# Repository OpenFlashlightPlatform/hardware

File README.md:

# Blue Sun OFP

The Blue Sun Open Flashlight Platform is an open source (both hardware and software)
attempt at creating a software-defined ultra-reliable high-performance flashlight.

This project was inspired by the AvE Midnight Sun project, and is intended to match
with the mechanicals developed there, both physically and in spirit. To that end,
a core set of specifications were identified:

 0. The project must be fun. This rule can be applied to override any subsequent
    rule.
 1. The design must be skookum. If in doubt as to the actual definition of "skookum"
    just go balls to the wall and hope the result is sufficiently epic.
 2. The platform should be capable of driving a diverse range of COBs at up to
    160W (40V / 4A). Ensure that in every aspect of the circuit, rule 1 is
    strongly enforced, so that excursions beyond 160W are tolerated and the
    circuit can dynamically detect and react to overload.
 3. The driver should have fine-grained current-mode control of the COB.
 4. The platform should operate from a 3s LiPo battery, and be capable of charging it
    from a 12V source. Naturally, transients, noise and polarity inversions on this
    source must be tolerated. Furthermore, all best practices for LiPo operation
    must be followed including UVLO, cell balancing and temperature monitoring.
 5. The platform should be accessible and open source at every possible level.
    To that end, it should be compatible out-of-the box with an Arduino IDE
    and programmable without any non-free tools, software or licenses.
 6. The circuit must be implemented in the spirit of Rule 1. Everything must be
    resistant to temperature, humidity, vibration, ESD, overvoltage, cell imbalance,
    and short circuit. The circuit must continue to function after being shaken
    in a container of salty boiling water mixed with conductive metal powder.
 7. Every net in the circuit, including internal nets and power supply rails,
    must pass IEC 61000-4-2 (25kV) and IEC 61004-4 (40A) ESD resistance tests.
 8. The firmware itself, both in source form and compiled form, must adhere to
    rule 1. In particular, wherever possible (in that it does not contradict rule
    5), the firmware should be MISRA C:2012 compliant.
 9. Every aspect of the project must be well documented. If the primary maintainer
    were to become unavailable, the community ought to be able to pick up and
    continue.

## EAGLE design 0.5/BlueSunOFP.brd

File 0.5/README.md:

# Version 0.5

This is a prototype iteration, that has no battery charging features. It is so that I can work on the hardware and firmware in parallel.

It should in theory work for up to 160W COBs. I'll be testing that at a later stage.

The BOM is also available as a google doc here: https://goo.gl/zxzSkw

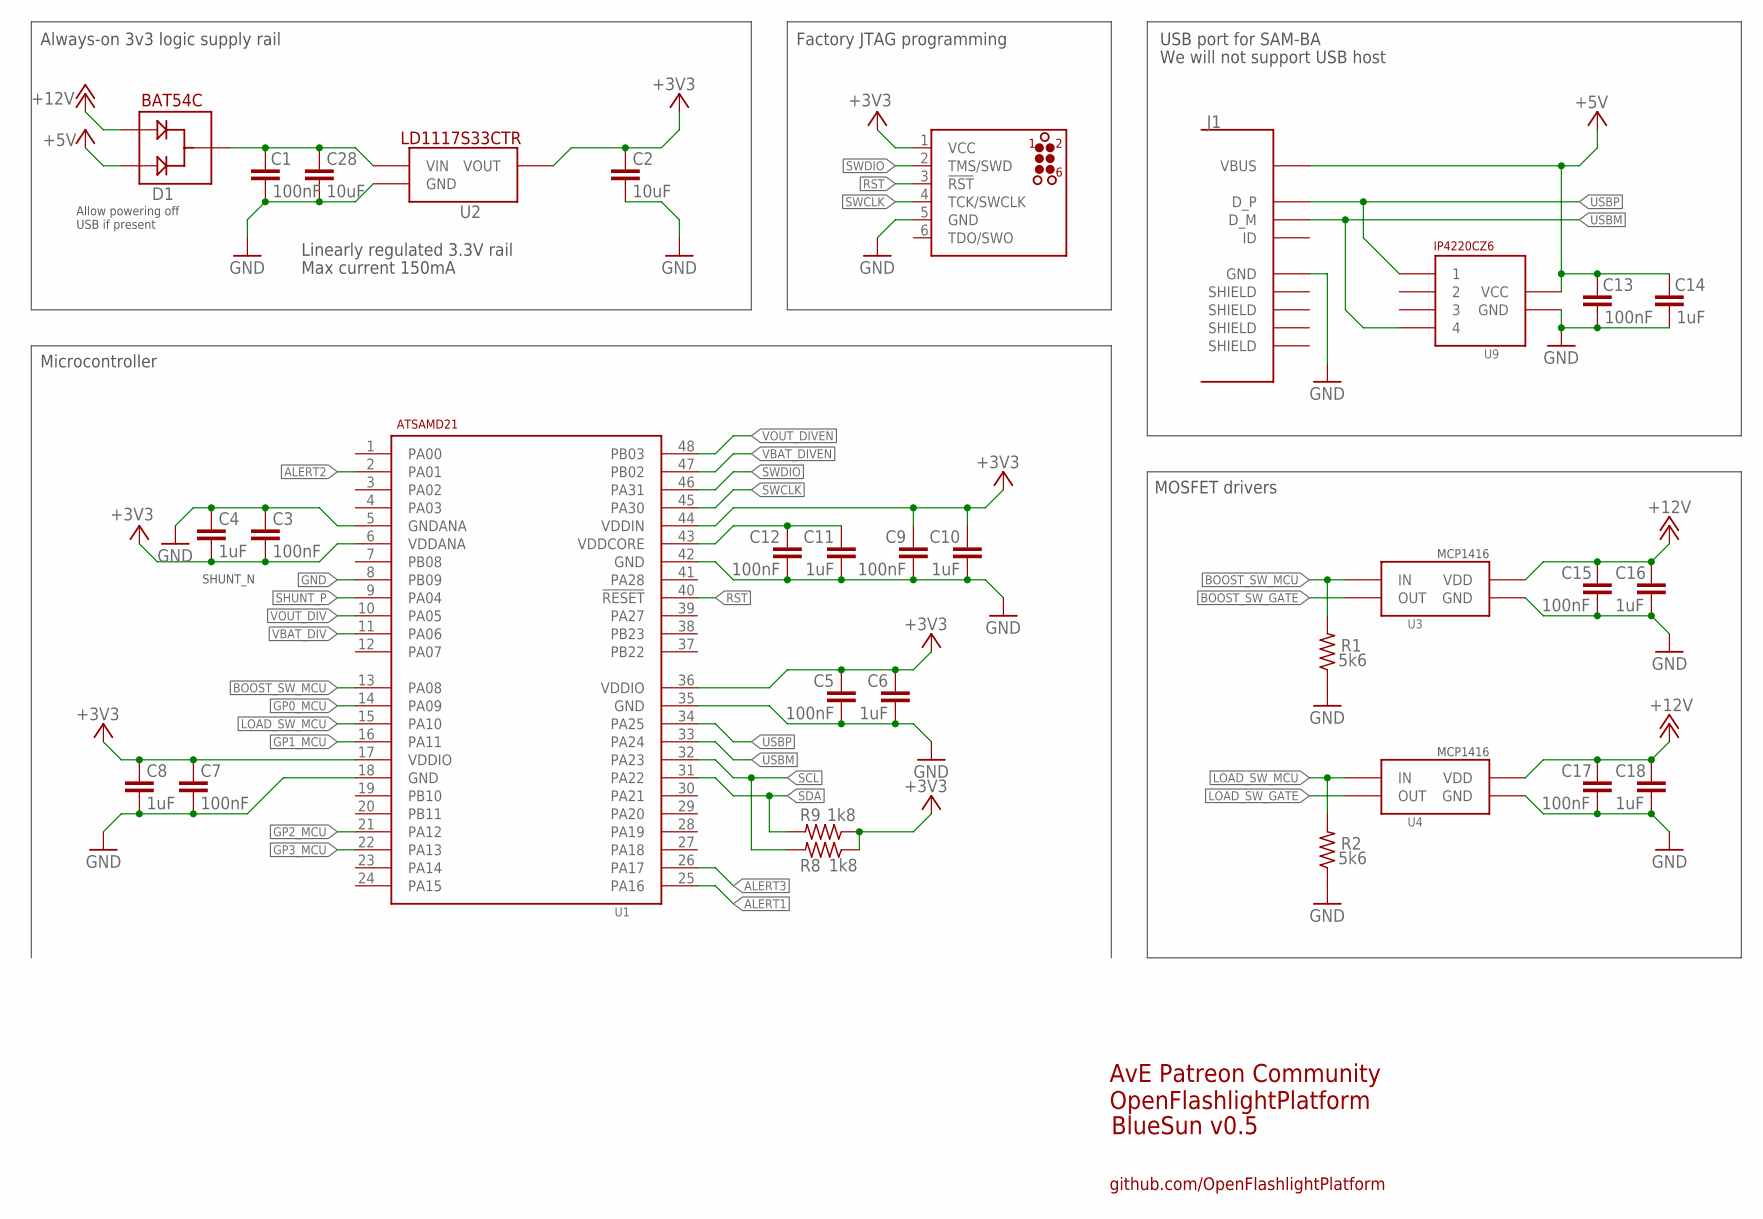
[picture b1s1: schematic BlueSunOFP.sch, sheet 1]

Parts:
C1, C13, C15, C17: 100nF; C0603K
C2, C28: 10uF; C0603K
C3, C5, C7, C9, C12: 100nF; C0402K
C4, C6, C8, C10, C11: 1uF; C0402K
C14, C16, C18: 1uF; C0603K
D1: BAT54C; SOT23
J1: USBSMT; USB_SMT
R1, R2: 5k6; R0603
R8, R9: 1k8; R0603
U1: SAMD21; TQFP48
U2: LD1117S33CTR_3V3_REG; SOT223
U3, U4: MCP1416; SOT23-5
U9: IP4220CZ6; SOT457
U$1: JLINK_CONNECT; TC2030-MCP-NL

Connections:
+3V3: C2.1, C3.2, C4.2, C5.1, C6.1, C7.1, C8.1, C9.1, C10.1, R8.1, R9.1, U1.6 (VDDANA), U1.17 (VDDIO), U1.36 (VDDIO), U1.44 (VDDIN), U2.2 (VOUT), U$1.1 (VCC); also elsewhere on the board
+5V: C13.1, C14.1, D1.2, J1.1VBUS (VBUS), U9.5 (VCC)
+12V: C15.1, C16.1, C17.1, C18.1, D1.1, U3.2 (VDD), U4.2 (VDD); also elsewhere on the board
ALERT1: U1.25 (PA16); also elsewhere on the board
ALERT2: U1.2 (PA01); also elsewhere on the board
ALERT3: U1.26 (PA17); also elsewhere on the board
BOOST_SW_GATE: U3.5 (OUT); also elsewhere on the board
BOOST_SW_MCU: R1.2, U1.13 (PA08), U3.3 (IN)
GND: C1.2, C2.2, C3.1, C4.1, C5.2, C6.2, C7.2, C8.2, C9.2, C10.2, C11.2, C12.2, C13.2, C14.2, C15.2, C16.2, C17.2, C18.2, C28.2, J1.5GND (GND), R1.1, R2.1, U1.5 (GNDANA), U1.8 (PB09), U1.18 (GND), U1.35 (GND), U1.42 (GND), U2.1 (GND), U3.4 (GND), U4.4 (GND), U9.2 (GND), U$1.5 (GND); also elsewhere on the board
GP0_MCU: U1.14 (PA09); also elsewhere on the board
GP1_MCU: U1.16 (PA11); also elsewhere on the board
GP2_MCU: U1.21 (PA12); also elsewhere on the board
GP3_MCU: U1.22 (PA13); also elsewhere on the board
LOAD_SW_GATE: U4.5 (OUT); also elsewhere on the board
LOAD_SW_MCU: R2.2, U1.15 (PA10), U4.3 (IN)
unnamed: C11.1, C12.1, U1.43 (VDDCORE)
unnamed: C1.1, C28.1, D1.3 (NEG), U2.3 (VIN)
RST: U1.40 (!RESET!), U$1.3 (!RST!)
SCL: R8.2, U1.32 (PA23); also elsewhere on the board
SDA: R9.2, U1.31 (PA22); also elsewhere on the board
SHUNT_P: U1.9 (PA04); also elsewhere on the board
SWCLK: U1.45 (PA30), U$1.4 (TCK/SWCLK)
SWDIO: U1.46 (PA31), U$1.2 (TMS/SWD)
USBM: J1.2D- (D_M), U1.33 (PA24), U9.6 (4)
USBP: J1.3D+ (D_P), U1.34 (PA25), U9.1
VBAT_DIV: U1.11 (PA06); also elsewhere on the board
VBAT_DIVEN: U1.47 (PB02); also elsewhere on the board
VOUT_DIV: U1.10 (PA05); also elsewhere on the board
VOUT_DIVEN: U1.48 (PB03); also elsewhere on the board

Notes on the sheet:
AvE Patreon Community
OpenFlashlightPlatform
BlueSun v0.5
github.com/OpenFlashlightPlatform
Linearly regulated 3.3V rail
Max current 150mA
Always-on 3v3 logic supply rail
Factory JTAG programming
Allow powering off USB if present
We will not support USB host
USB port for SAM-BA
MOSFET drivers
Microcontroller
SHUNT_N

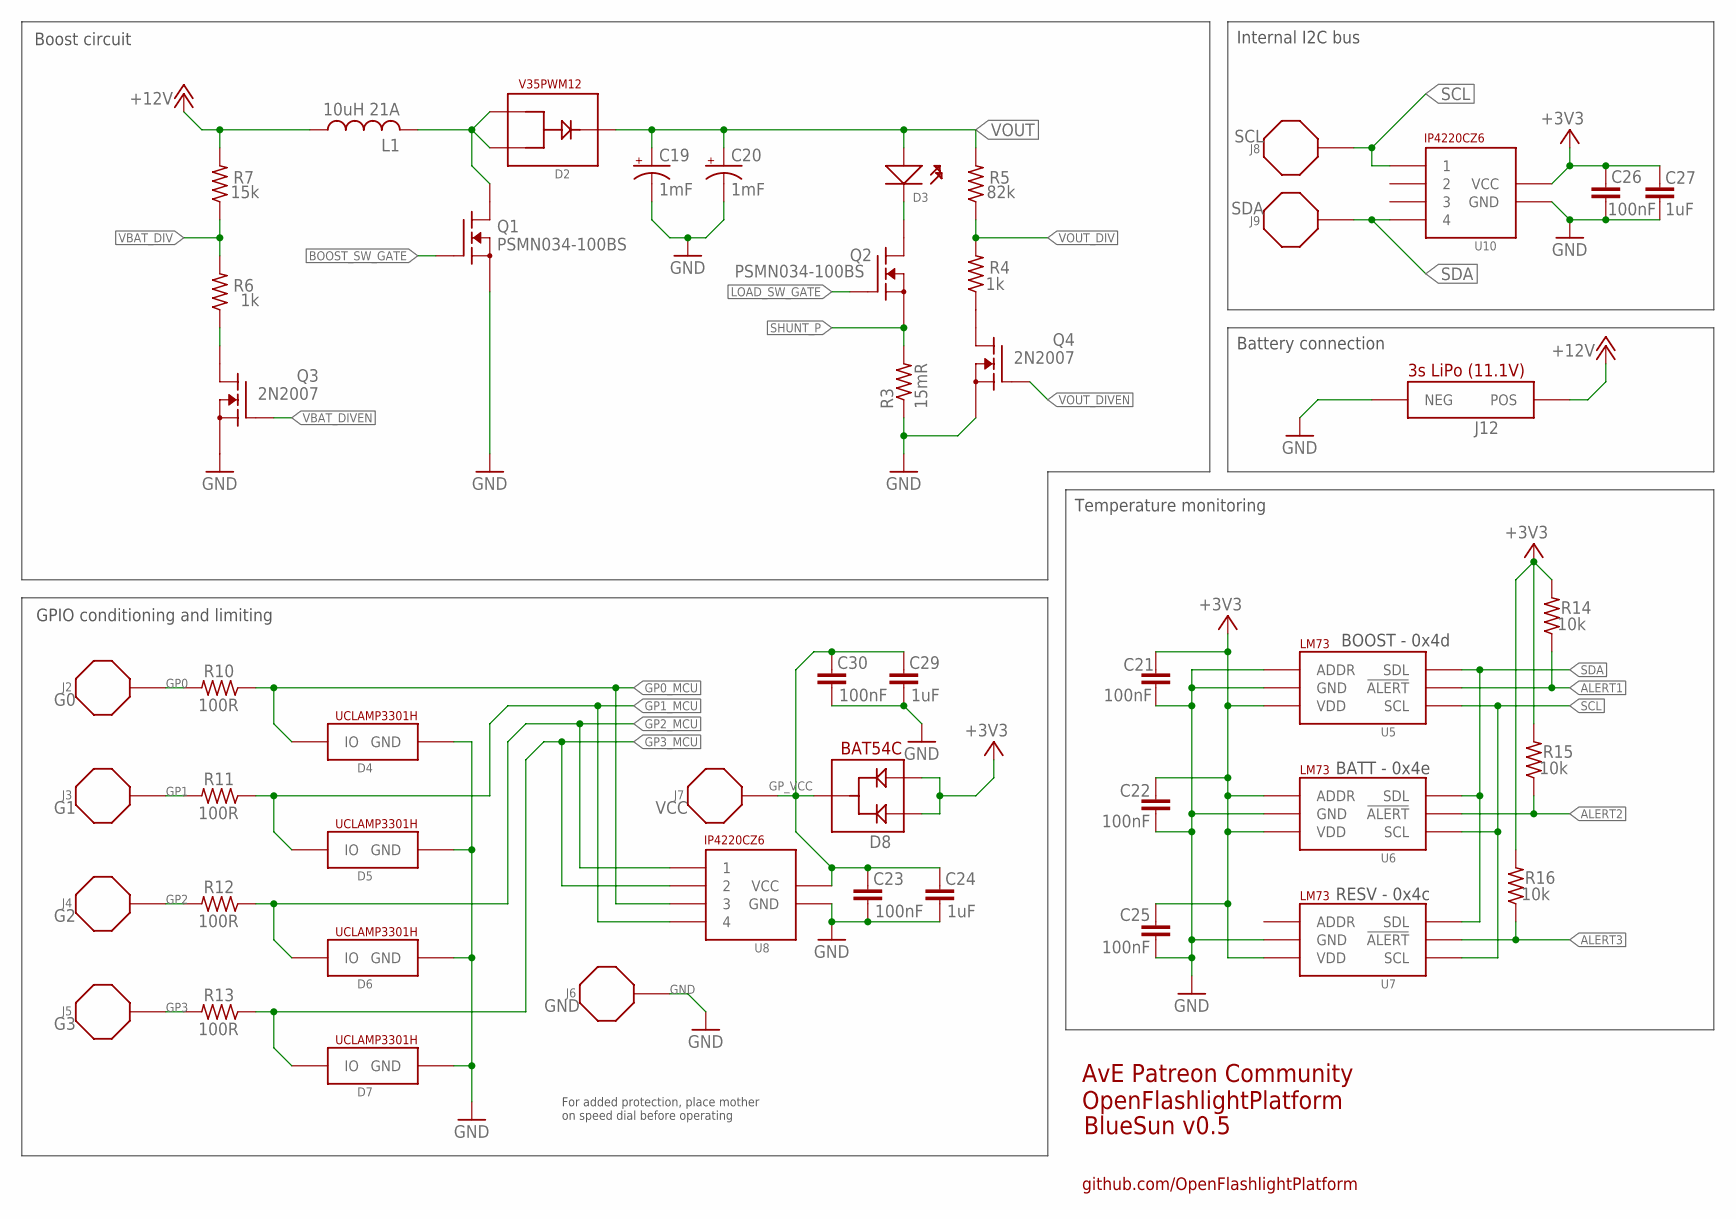
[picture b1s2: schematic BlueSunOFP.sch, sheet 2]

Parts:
C19, C20: 1mF; 10MMCAP
C21, C22, C23, C25, C26, C30: 100nF; C0603K
C24, C27, C29: 1uF; C0603K
D2: DIODE; SLIMPAK
D3: CREE_COB; CREE_WIRE_MOUNT
D4, D5, D6, D7: UCLAMP3301H; SOD523
D8: BAT54C; SOT23
J2: G0; EXT_PIN
J3: G1; EXT_PIN
J4: G2; EXT_PIN
J5: G3; EXT_PIN
J6: GND; EXT_PIN
J7: VCC; EXT_PIN
J8: SCL; EXT_PIN
J9: SDA; EXT_PIN
J12: BATTERY; CREE_WIRE_MOUNT
L1: 10uH 21A; INDUCTOR
Q1, Q2: PSMN034-100BS; D2PAK
Q3, Q4: 2N2007; SOT23
R3: 15mR; R2512
R4, R6: 1k; R0603
R5: 82k; R0603
R7: 15k; R0603
R10, R11, R12, R13: 100R; R0603
R14, R15, R16: 10k; R0603
U5, U6, U7: LM73; SOT23-6
U8, U10: IP4220CZ6; SOT457

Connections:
+3V3: C21.1, C22.1, C25.1, C26.1, C27.1, D8.1, D8.2, R14.2, R15.2, R16.2, U5.3 (VDD), U6.1 (ADDR), U6.3 (VDD), U7.3 (VDD), U10.5 (VCC); also elsewhere on the board
+12V: J12.POS, L1.P$1 (1), R7.2; also elsewhere on the board
ALERT1: R14.1, U5.5 (!ALERT!); also elsewhere on the board
ALERT2: R15.1, U6.5 (!ALERT!); also elsewhere on the board
ALERT3: R16.1, U7.5 (!ALERT!); also elsewhere on the board
BOOST_SW_GATE: Q1.1 (G); also elsewhere on the board
GND: C19.NEG (-), C20.NEG (-), C21.2, C22.2, C23.2, C24.2, C25.2, C26.2, C27.2, C29.2, C30.2, D4.NOLINE (GND), D5.NOLINE (GND), D6.NOLINE (GND), D7.NOLINE (GND), J6.P$1, J12.NEG, Q1.3 (S), Q3.2 (S), Q4.2 (S), R3.1, U5.1 (ADDR), U5.2 (GND), U6.2 (GND), U7.2 (GND), U8.2 (GND), U10.2 (GND); also elsewhere on the board
GP0: J2.P$1, R10.2
GP0_MCU: D4.LINE (IO), R10.1, U8.4 (3); also elsewhere on the board
GP1: J3.P$1, R11.2
GP1_MCU: D5.LINE (IO), R11.1, U8.6 (4); also elsewhere on the board
GP2: J4.P$1, R12.2
GP2_MCU: D6.LINE (IO), R12.1, U8.1; also elsewhere on the board
GP3: J5.P$1, R13.2
GP3_MCU: D7.LINE (IO), R13.1, U8.3 (2); also elsewhere on the board
GP_VCC: C23.1, C24.1, C29.1, C30.1, D8.3 (NEG), J7.P$1, U8.5 (VCC)
LOAD_SW_GATE: Q2.1 (G); also elsewhere on the board
unnamed: D2.1, D2.2, L1.P$2 (2), Q1.2 (D)
unnamed: D3.NEG, Q2.2 (D)
unnamed: Q3.3 (D), R6.1
unnamed: Q4.3 (D), R4.1
SCL: J8.P$1, U5.4 (SCL), U6.4 (SCL), U7.4 (SCL), U10.1; also elsewhere on the board
SDA: J9.P$1, U5.6 (SDL), U6.6 (SDL), U7.6 (SDL), U10.6 (4); also elsewhere on the board
SHUNT_P: Q2.3 (S), R3.2; also elsewhere on the board
VBAT_DIV: R6.2, R7.1; also elsewhere on the board
VBAT_DIVEN: Q3.1 (G); also elsewhere on the board
VOUT: C19.POS (+), C20.POS (+), D2.K, D3.POS, R5.2
VOUT_DIV: R4.2, R5.1; also elsewhere on the board
VOUT_DIVEN: Q4.1 (G); also elsewhere on the board

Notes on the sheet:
AvE Patreon Community
OpenFlashlightPlatform
BlueSun v0.5
github.com/OpenFlashlightPlatform
For added protection, place mother on speed dial before operating
GPIO conditioning and limiting
Boost circuit
BOOST - 0x4d
BATT - 0x4e
RESV - 0x4c
Temperature monitoring
Internal I2C bus
Battery connection

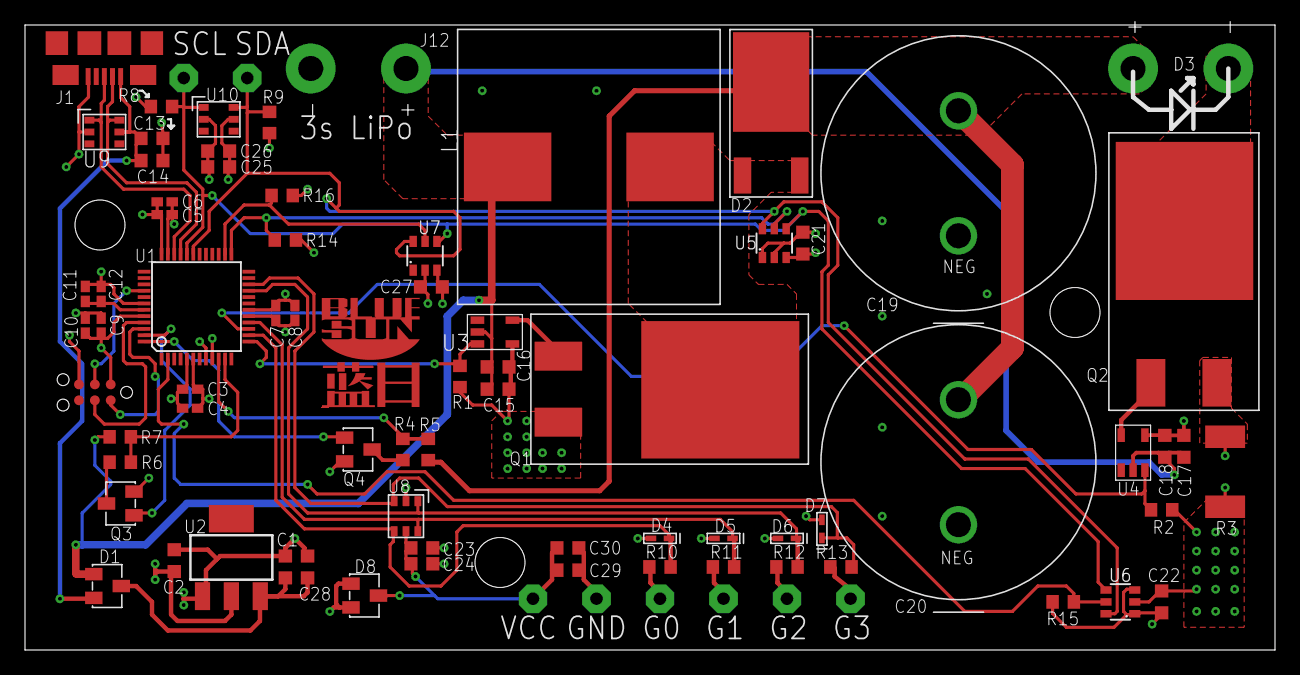
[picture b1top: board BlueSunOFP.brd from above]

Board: 4 copper layers, 100.0 x 50.0 mm, 80 parts (0 on the bottom side), 39 nets.

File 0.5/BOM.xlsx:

Nothing fancy passives, any brand will do
Designator | Type | Notes
C1, C15, C17 | 100nF 25V 0603 X7R
C28 | 10uF 25V 0805 X5R | The pad is 0603, my bad
C16, C18 | 1uF 25V 0603 X7R
C2 | 10uF 6V3 0603 X5R
C3, C5, C7, C9, C12, C13, C21, C22, C23, C25, C26, C30 | 100nF 6V3 0603 X7R
C4, C6, C8, C10, C11, C14, C24, C27, C29 | 1uF 6V3 0603 X7R
R1, R2 | 5k6 0603 1%
R4, R6 | 1k 0603 1%
R5 | 82k 0603 1%
R7 | 15k 0603 1%
R8, R9 | 1k8 0603 1%
R10, R11, R12, R13 | 100R 0603 1%
R14, R15, R16 | 10k 0603 1%
Specific parts
Designator | Type | Manufacturer | MFG part no | Digikey part no | Price/100 USD | Qty | Notes
C19, C20 | 1mF 80V 10mm cap | CDE | 381LX102M080H012 | 338-3690-ND | 1.7 | 2.0
D1, D8 | SOT23 Schottky | Fairchild | BAT54C | BAT54CFSTR-ND | 0.09 | 2.0
D4, D5, D6, D7 | TVS diode 3.3V | Semtech | UCLAMP3301H.TCT | UCLAMP3301HCT-ND | 0.48 | 4.0
D2 | Big SlimDPAK schottky | Vishay | V35PWM12-M3/I | V35PWM12-M3/IGITR-ND | 0.88 | 1.0
J1 | SMT USB micro | Amphenol | 10118192-0001LF | 609-4613-1-ND | 0.3 | 1.0
L1 | 10uH 21A inductor | Wurth | 74435581000 | 732-4235-2-ND | 6.6 | 1.0
Q1, Q2 | Power MOSFET | NXP | PSMN034-100BS,118 | 568-9702-2-ND | 0.71 | 2.0
Q3, Q4 | Signal MOSFET | NXP | 2N7002P,215 | 568-5818-1-ND | 0.07 | 2.0
U1 | MCU | Atmel | ATSAMD21G18A-AUT | ATSAMD21G18A-AUTCT-ND | 4.15 | 1.0
U2 | LDO | ST Micro | LD1117S33CTR | 497-1241-1-ND | 0.25 | 1.0
U3, U4 | MOSFET driver | Microchip | MCP1416T-E/OT | MCP1416T-E/OTTR-ND | 0.49 | 2.0
U5, U6, U7 | Temp sensor | TI | LM73CIMK-1/NOPB | LM73CIMK-1/NOPBCT-ND | 1.48 | 3.0
U8, U9, U10 | Steering / TVS | NXP | IP4220CZ6,125 | 568-3529-2-ND | 0.23 | 3.0
R3 | Shunt resistor 15mR | TE Connectivity | RLP73V3AR015FTDF | A109674CT-ND | 0.25 | 1.0
D3 | The COB 13 klm (!) | CREE | CXA3590-0000-000N00CD0E3 | CXA3590-0000-000N00CD0E3-ND | 37.18 | 1.0 | Any <40V <4A COB is ok

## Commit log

2016-11-17 Initial version
2016-11-17 add readme
2016-11-17 Add BOM and pdf schematic

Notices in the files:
parts and their libraries:
flashlight: ©2009 ROFA.cz
